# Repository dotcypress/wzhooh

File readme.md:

# Wzhooh

Slot Car Lap Timer

## Resources

- [Web dashboard](https://wzhooh.vercel.app)
- [Schematics](pcb/fab/wzhooh.pdf)
- [Gerber files](pcb/fab/Wzhooh_rev_0x01.zip)
- [BOM](pcb/fab/wzhooh-bom.csv)
- [Interactive BOM](https://htmlpreview.github.io/?https://github.com/dotcypress/wzhooh/blob/main/pcb/fab/ibom.html)

## Installation

1. Download latest firmware build from [Releases page](https://github.com/dotcypress/wzhooh/releases)
2. Hold the BOOTSEL button while connecting your board to the computer
3. Copy firmware file downloaded earlier to the RPi-RP2 disk
4. Enjoy

## Building firmware

1. Install rustup by following the instructions at https://rustup.rs
2. Install Cortex-M0, M0+, and M1 (ARMv6-M architecture) target: `rustup target add thumbv6m-none-eabi`
3. Install LLVM tools: `rustup component add llvm-tools-preview`
4. Install cargo-binutils: `cargo install cargo-binutils` (Note: on some Linux distros (e.g. Ubuntu) you may need to install the packages build-essential, gcc-arm-none-eabi, libssl-dev and pkg-config prior to installing cargo-binutils)
5. Install elf2uf2: `cargo install elf2uf2-rs`
6. Clone this repo: `git clone git@github.com:dotcypress/wzhooh.git && cd wzhooh`
7. Hold the BOOTSEL button while connecting your board to the computer
8. Flash microcontroller: `cargo run --release`

## License

Licensed under either of

- Apache License, Version 2.0 ([LICENSE-APACHE](LICENSE-APACHE) or
  http://www.apache.org/licenses/LICENSE-2.0)
- MIT license ([LICENSE-MIT](LICENSE-MIT) or http://opensource.org/licenses/MIT)

at your option.

### Contribution

Unless you explicitly state otherwise, any contribution intentionally submitted
for inclusion in the work by you, as defined in the Apache-2.0 license, shall be
dual licensed as above, without any additional terms or conditions.

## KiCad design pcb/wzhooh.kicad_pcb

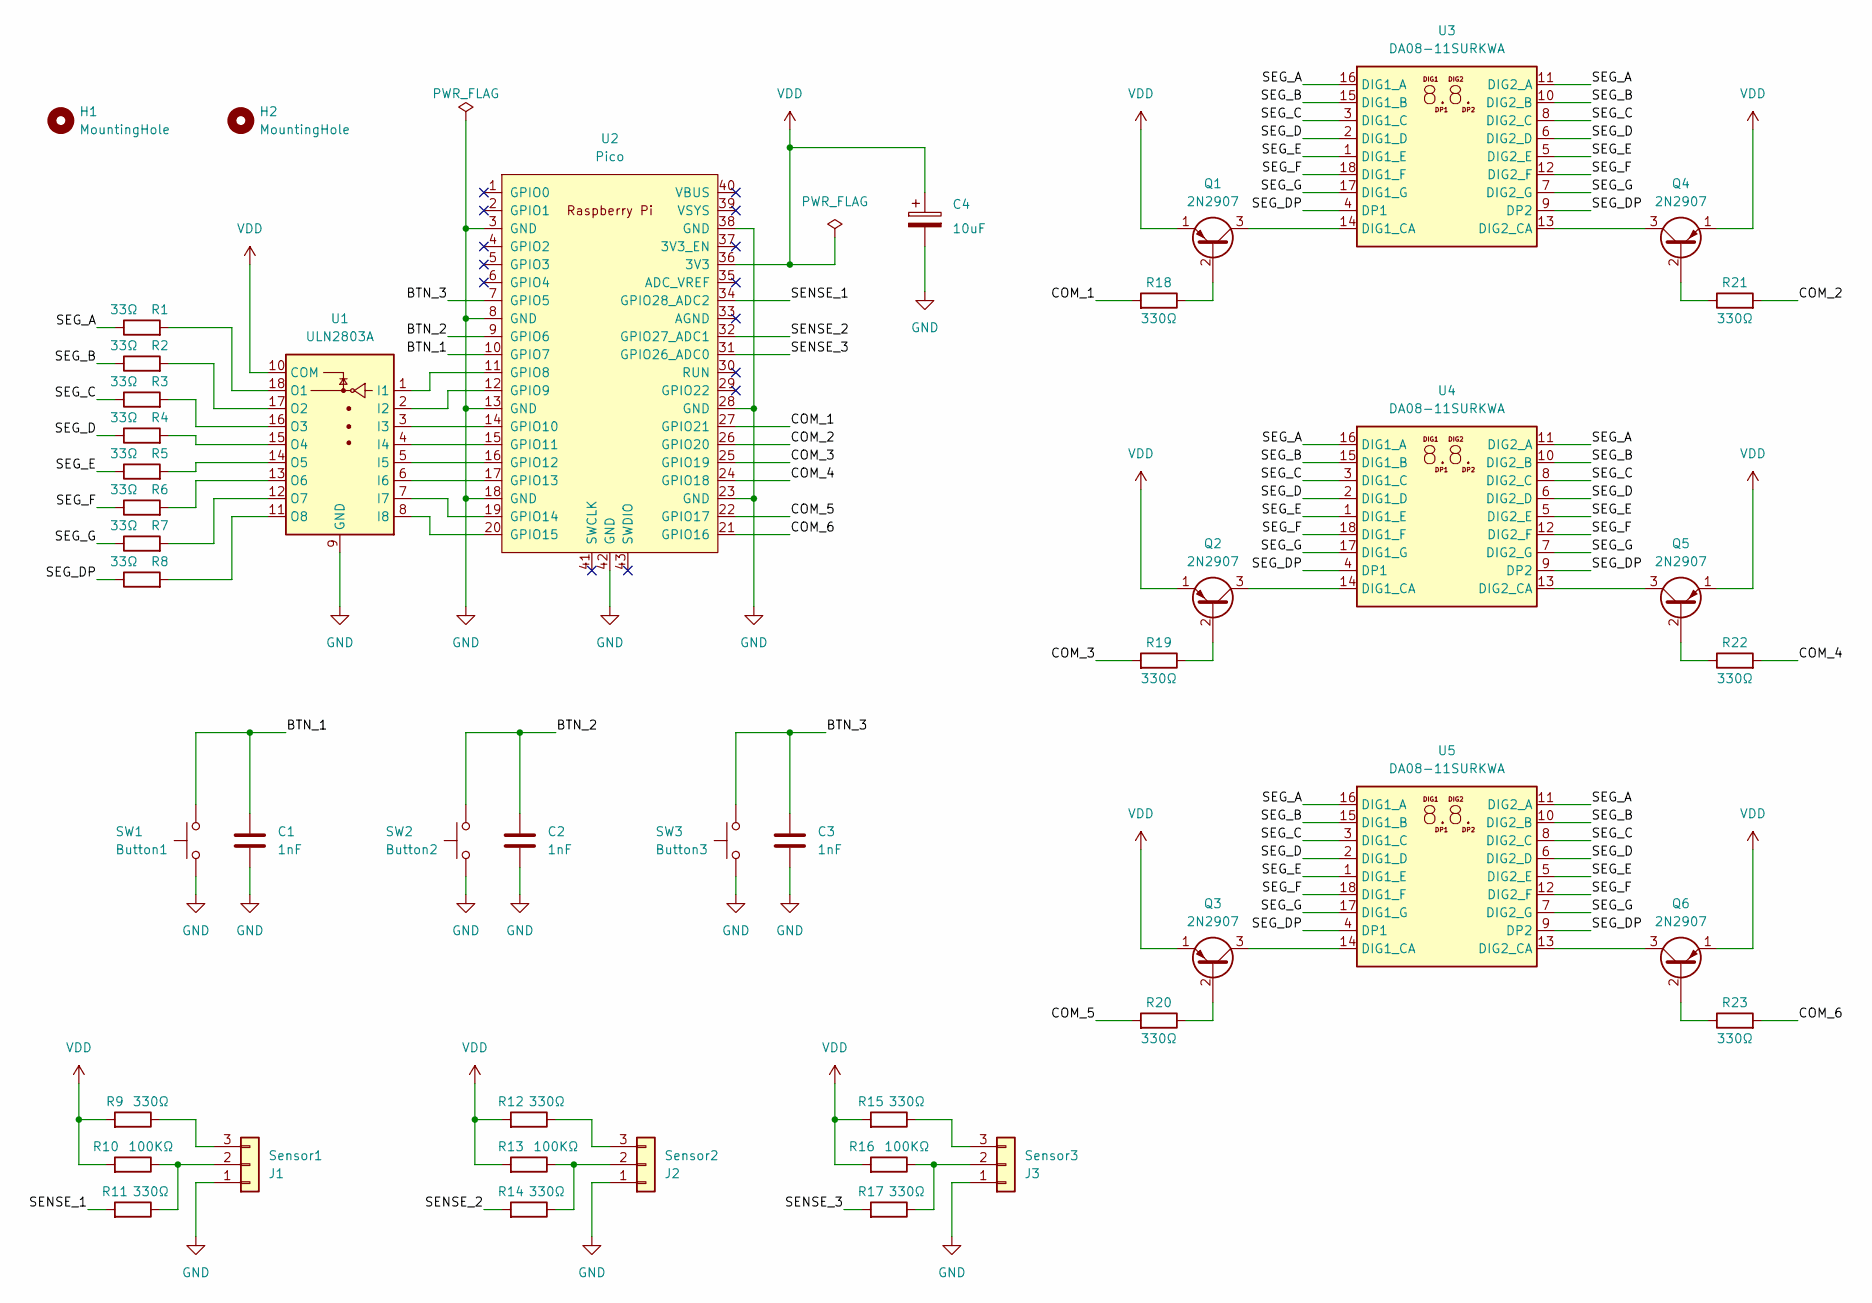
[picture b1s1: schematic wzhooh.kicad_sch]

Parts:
C1, C2, C3: 1nF; C_Disc_D4.7mm_W2.5mm_P5.00mm
C4: 10uF; CP_Radial_D7.5mm_P2.50mm
H1, H2: MountingHole; MountingHole_3.2mm_M3
J1: Sensor1; PinHeader_1x03_P2.54mm_Horizontal
J2: Sensor2; PinHeader_1x03_P2.54mm_Horizontal
J3: Sensor3; PinHeader_1x03_P2.54mm_Horizontal
Q1, Q2, Q3, Q4, Q5: 2N2907; TO-92_Inline
Q6: 2N2907; //www.mouser.com/datasheet/2/849/2n2907a-2577411.pdf
R1, R2, R3, R4, R5, R6, R7, R8: 33Ω; R_Axial_DIN0207_L6.3mm_D2.5mm_P2.54mm_Vertical
R9, R11, R12, R14, R15, R17, R18, R19, R20, R21, R22, R23: 330Ω; R_Axial_DIN0207_L6.3mm_D2.5mm_P2.54mm_Vertical
R10, R13, R16: 100KΩ; R_Axial_DIN0207_L6.3mm_D2.5mm_P2.54mm_Vertical
SW1: Button1; SW_PUSH_6mm_H13mm
SW2: Button2; SW_PUSH_6mm_H13mm
SW3: Button3; SW_PUSH_6mm_H13mm
U1: ULN2803A; DIP-18_W7.62mm
U2: Pico; RPi_Pico_SMD_TH
U3, U4, U5: DA08-11SURKWA; DA08-11

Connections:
/BTN_1: C1.1, SW1.2, U2.10 (GPIO7)
/BTN_2: C2.1, SW2.2, U2.9 (GPIO6)
/BTN_3: C3.1, SW3.2, U2.7 (GPIO5)
/COM_1: R18.2, U2.27 (GPIO21)
/COM_2: R21.2, U2.26 (GPIO20)
/COM_3: R19.2, U2.25 (GPIO19)
/COM_4: R22.2, U2.24 (GPIO18)
/COM_5: R20.2, U2.22 (GPIO17)
/COM_6: R23.2, U2.21 (GPIO16)
/SEG_A: R1.1, U3.11 (DIG2_A), U3.16 (DIG1_A), U4.11 (DIG2_A), U4.16 (DIG1_A), U5.11 (DIG2_A), U5.16 (DIG1_A)
/SEG_B: R2.1, U3.10 (DIG2_B), U3.15 (DIG1_B), U4.10 (DIG2_B), U4.15 (DIG1_B), U5.10 (DIG2_B), U5.15 (DIG1_B)
/SEG_C: R3.1, U3.3 (DIG1_C), U3.8 (DIG2_C), U4.3 (DIG1_C), U4.8 (DIG2_C), U5.3 (DIG1_C), U5.8 (DIG2_C)
/SEG_D: R4.1, U3.2 (DIG1_D), U3.6 (DIG2_D), U4.2 (DIG1_D), U4.6 (DIG2_D), U5.2 (DIG1_D), U5.6 (DIG2_D)
/SEG_DP: R8.1, U3.4 (DP1), U3.9 (DP2), U4.4 (DP1), U4.9 (DP2), U5.4 (DP1), U5.9 (DP2)
/SEG_E: R5.1, U3.1 (DIG1_E), U3.5 (DIG2_E), U4.1 (DIG1_E), U4.5 (DIG2_E), U5.1 (DIG1_E), U5.5 (DIG2_E)
/SEG_F: R6.1, U3.12 (DIG2_F), U3.18 (DIG1_F), U4.12 (DIG2_F), U4.18 (DIG1_F), U5.12 (DIG2_F), U5.18 (DIG1_F)
/SEG_G: R7.1, U3.7 (DIG2_G), U3.17 (DIG1_G), U4.7 (DIG2_G), U4.17 (DIG1_G), U5.7 (DIG2_G), U5.17 (DIG1_G)
/SENSE_1: R11.2, U2.34 (GPIO28_ADC2)
/SENSE_2: R14.2, U2.32 (GPIO27_ADC1)
/SENSE_3: R17.2, U2.31 (GPIO26_ADC0)
GND: C1.2, C2.2, C3.2, C4.2, J1.1, J2.1, J3.1, SW1.1, SW2.1, SW3.1, U1.9 (GND), U2.3 (GND), U2.8 (GND), U2.13 (GND), U2.18 (GND), U2.23 (GND), U2.28 (GND), U2.38 (GND), U2.42 (GND)
unnamed: J1.2, R10.1, R11.1
unnamed: J1.3, R9.1
unnamed: J2.2, R13.1, R14.1
unnamed: J2.3, R12.1
unnamed: J3.2, R16.1, R17.1
unnamed: J3.3, R15.1
unnamed: Q1.2 (B), R18.1
unnamed: Q1.3 (C), U3.14 (DIG1_CA)
unnamed: Q2.2 (B), R19.1
unnamed: Q2.3 (C), U4.14 (DIG1_CA)
unnamed: Q3.2 (B), R20.1
unnamed: Q3.3 (C), U5.14 (DIG1_CA)
unnamed: Q4.2 (B), R21.1
unnamed: Q4.3 (C), U3.13 (DIG2_CA)
unnamed: Q5.2 (B), R22.1
unnamed: Q5.3 (C), U4.13 (DIG2_CA)
unnamed: Q6.2 (B), R23.1
unnamed: Q6.3 (C), U5.13 (DIG2_CA)
unnamed: U1.1 (I1), U2.11 (GPIO8)
unnamed: U1.2 (I2), U2.12 (GPIO9)
unnamed: U1.3 (I3), U2.14 (GPIO10)
unnamed: U1.4 (I4), U2.15 (GPIO11)
unnamed: U1.5 (I5), U2.16 (GPIO12)
unnamed: U1.6 (I6), U2.17 (GPIO13)
unnamed: U1.7 (I7), U2.19 (GPIO14)
unnamed: U1.8 (I8), U2.20 (GPIO15)
unnamed: R1.2, U1.18 (O1)
unnamed: R2.2, U1.17 (O2)
unnamed: R3.2, U1.16 (O3)
unnamed: R4.2, U1.15 (O4)
unnamed: R5.2, U1.14 (O5)
unnamed: R6.2, U1.13 (O6)
unnamed: R7.2, U1.12 (O7)
unnamed: R8.2, U1.11 (O8)
VDD: C4.1, Q1.1 (E), Q2.1 (E), Q3.1 (E), Q4.1 (E), Q5.1 (E), Q6.1 (E), R9.2, R10.2, R12.2, R13.2, R15.2, R16.2, U1.10 (COM), U2.36 (3V3)

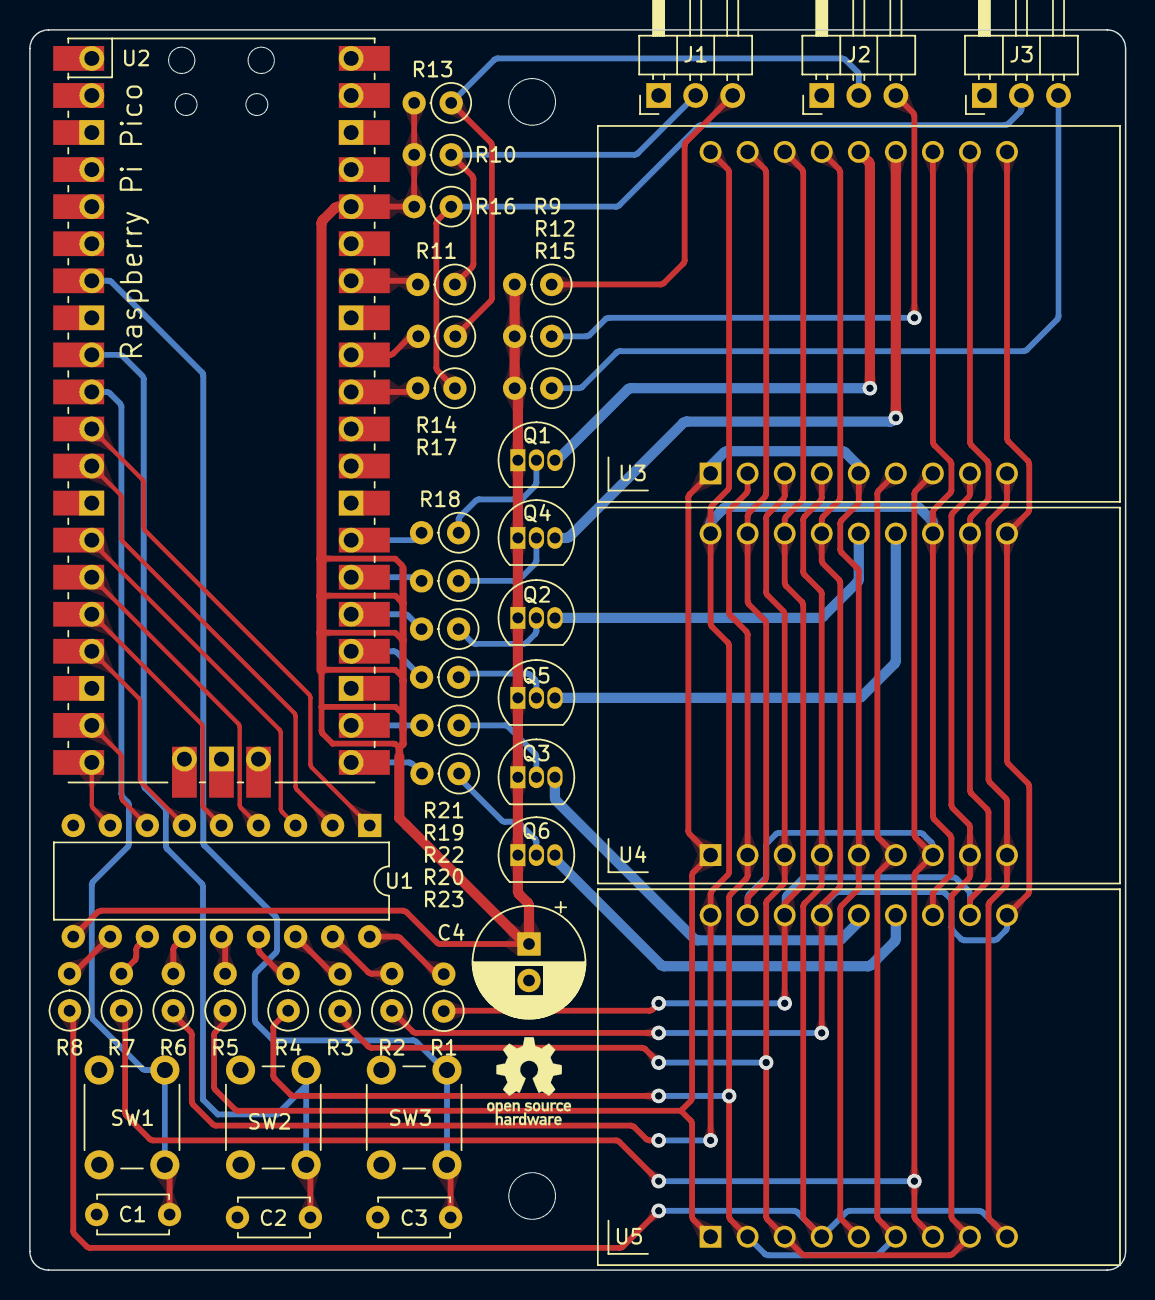
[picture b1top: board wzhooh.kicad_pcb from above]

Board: 2 copper layers, 75.1 x 85.0 mm, 46 parts (0 on the bottom side), 56 nets.

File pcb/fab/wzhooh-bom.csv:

Id,Designator,Footprint,Quantity,Designation,Supplier and ref,,
1,"R11,R22,R20,R21,R14,R12,R9,R17,R19,R18,R23,R15",R_Axial_DIN0207_L6.3mm_D2.5mm_P2.54mm_Vertical,12,330Ω,https://m-teh.com.ua/ru/rezistor-330r-0.25w-cfr-5,,
2,"R4,R6,R8,R7,R5,R3,R2,R1",R_Axial_DIN0207_L6.3mm_D2.5mm_P2.54mm_Vertical,8,33Ω,https://m-teh.com.ua/ru/rezistor-33r-0.25w-cfr-5/,,
6,"C3,C1,C2",C_Disc_D4.7mm_W2.5mm_P5.00mm,3,1nF,https://m-teh.com.ua/ru/kondensator-mcc-0.1uf-50v-x7r-10/,,
7,C4,CP_Radial_D7.5mm_P2.50mm,1,4.7uF,https://m-teh.com.ua/ru/kondensator-ze-330uf-10v-69-[polimerniy]/,,
8,"J1,J2,J3",PinHeader_1x03_P2.54mm_Horizontal,3,Sensors,https://m-teh.com.ua/ru/pls1x40-zl201-40g/,,
9,"U4,U5,U3",DA08-11,3,DA08-11SURKWA,https://m-teh.com.ua/ru/indikator-2-rozryadi-0.8chervoniy-an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,,
10,"R10,R16,R13",R_Axial_DIN0207_L6.3mm_D2.5mm_P2.54mm_Vertical,3,100KΩ,https://m-teh.com.ua/ru/rezistor-100k-0.25w-cfr-5,,
11,"Q3,Q1,Q2,Q4,Q6,Q5",TO-92_Inline,6,2N2907,https://m-teh.com.ua/ru/tranzistor-2n2907/,,
12,U2,RPi_Pico_SMD_TH,1,Pico,https://arduino.ua/prod4358-raspberry-pi-pico,,
13,"SW1,SW2,SW3",SW_PUSH_6mm_H13mm,3,Buttons,https://m-teh.com.ua/ru/knopka-taktova-tact-6x6-7.5,,
16,U1,DIP-18_W7.62mm,1,ULN2803A,https://m-teh.com.ua/ru/sborka-tranzystorov-uln2803apg,,

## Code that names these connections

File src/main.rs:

#![no_std]
#![no_main]

extern crate panic_probe;
extern crate rp2040_hal as hal;
extern crate rtic;

use defmt_rtt as _;

mod counter;
mod display;
mod io;
mod telemetry;

use cortex_m::singleton;
use counter::*;
use display::*;
use embedded_hal::digital::v2::OutputPin;
use hal::gpio::*;
use hal::pac;
use hal::pwm;
use hal::timer::{monotonic::Monotonic, *};
use hal::usb::UsbBus;
use io::*;
use telemetry::*;
use usb_device::class_prelude::*;
use usb_device::prelude::*;
use usbd_webusb::{url_scheme, WebUsb};

pub const XTAL_FREQ_HZ: u32 = 12_000_000_u32;

#[link_section = ".boot2"]
#[no_mangle]
#[used]
pub static BOOT2: [u8; 256] = rp2040_boot2::BOOT_LOADER_GENERIC_03H;

#[rtic::app(device = pac, peripherals = true, dispatchers = [SW0_IRQ, SW1_IRQ])]
mod app {
    use super::*;

    #[monotonic(binds = TIMER_IRQ_0, default = true)]
    type Oracle = Monotonic<Alarm0>;

    #[local]
    struct Local {
        buttons: Buttons,
        sensors: Sensors,
        ui_timer: pwm::Slice<pwm::Pwm0, pwm::FreeRunning>,
        usb_dev: UsbDevice<'static, hal::usb::UsbBus>,
        wusb: WebUsb<hal::usb::UsbBus>,
    }

    #[shared]
    struct Shared {
        display: Display,
        counter: LapCounter,
        telemetry: RaceTelemetryClass<'static, hal::usb::UsbBus>,
    }

    #[init]
    fn init(ctx: init::Context) -> (Shared, Local, init::Monotonics) {
        let mut resets = ctx.device.RESETS;
        let mut watchdog = hal::Watchdog::new(ctx.device.WATCHDOG);
        let clocks = hal::clocks::init_clocks_and_plls(
            XTAL_FREQ_HZ,
            ctx.device.XOSC,
            ctx.device.CLOCKS,
            ctx.device.PLL_SYS,
            ctx.device.PLL_USB,
            &mut resets,
            &mut watchdog,
        )
        .ok()
        .expect("Clocks init failed");

        let sio = hal::Sio::new(ctx.device.SIO);
        let pins = Pins::new(
            ctx.device.IO_BANK0,
            ctx.device.PADS_BANK0,
            sio.gpio_bank0,
            &mut resets,
        );

        let counter = LapCounter::default();

        let sensors = Sensors::new([
            pins.gpio28.into_floating_input().into_dyn_pin(),
            pins.gpio27.into_floating_input().into_dyn_pin(),
            pins.gpio26.into_floating_input().into_dyn_pin(),
        ]);

        let buttons = Buttons::new([
            pins.gpio7.into_pull_up_input().into_dyn_pin(),
            pins.gpio6.into_pull_up_input().into_dyn_pin(),
            pins.gpio5.into_pull_up_input().into_dyn_pin(),
        ]);

        let display = Display::new(
            [
                pins.gpio20.into_push_pull_output().into_dyn_pin(),
                pins.gpio21.into_push_pull_output().into_dyn_pin(),
                pins.gpio18.into_push_pull_output().into_dyn_pin(),
                pins.gpio19.into_push_pull_output().into_dyn_pin(),
                pins.gpio16.into_push_pull_output().into_dyn_pin(),
                pins.gpio17.into_push_pull_output().into_dyn_pin(),
            ],
            [
                pins.gpio8.into_push_pull_output().into_dyn_pin(),
                pins.gpio9.into_push_pull_output().into_dyn_pin(),
                pins.gpio10.into_push_pull_output().into_dyn_pin(),
                pins.gpio11.into_push_pull_output().into_dyn_pin(),
                pins.gpio12.into_push_pull_output().into_dyn_pin(),
                pins.gpio13.into_push_pull_output().into_dyn_pin(),
                pins.gpio14.into_push_pull_output().into_dyn_pin(),
                pins.gpio15.into_push_pull_output().into_dyn_pin(),
            ],
        );

        let pwm_slices = hal::pwm::Slices::new(ctx.device.PWM, &mut resets);
        let mut ui_timer = pwm_slices.pwm0;
        ui_timer.enable_interrupt();
        ui_timer.enable();

        let mut timer = hal::Timer::new(ctx.device.TIMER, &mut resets, &clocks);
        let alarm = timer.alarm_0().expect("Alarm0 init failed");
        let mono = Monotonic::new(timer, alarm);

        let usb_regs = ctx.device.USBCTRL_REGS;
        let usb_dpram = ctx.device.USBCTRL_DPRAM;
        let usb_bus = UsbBus::new(usb_regs, usb_dpram, clocks.usb_clock, true, &mut resets);
        let usb_bus: &'static UsbBusAllocator<UsbBus> =
            singleton!(: UsbBusAllocator<UsbBus> = UsbBusAllocator::new(usb_bus))
                .expect("USB init failed");

        let wusb = WebUsb::new(usb_bus, url_scheme::HTTPS, "wzhooh.vercel.app");
        let telemetry = RaceTelemetryClass::new(usb_bus);

        let usb_dev = UsbDeviceBuilder::new(usb_bus, UsbVidPid(0x1209, 0xb421))
            .manufacturer("vitaly.codes")
            .product("Wzhooh")
            .serial_number("_wzhooh_")
            .build();

        unsafe {
            pac::NVIC::unmask(pac::Interrupt::IO_IRQ_BANK0);
            pac::NVIC::unmask(pac::Interrupt::USBCTRL_IRQ);
        };

        (
            Shared {
                counter,
                display,
                telemetry,
            },
            Local {
                buttons,
                sensors,
                wusb,
                ui_timer,
                usb_dev,
            },
            init::Monotonics(mono),
        )
    }

    #[task(binds = IO_IRQ_BANK0, priority = 3, local = [buttons, sensors])]
    fn io_irq(ctx: io_irq::Context) {
        let now = monotonics::now();
        for track in 0..TRACKS {
            if ctx.local.sensors.is_car_detected(track) {
                io_event::spawn(IoEvent::CarDetected(track, now)).ok();
            }
        }
        for button in [Button::A, Button::B, Button::C] {
            if ctx.local.buttons.is_pressed(button) {
                io_event::spawn(IoEvent::ButtonPressed(button)).ok();
            }
        }
    }

    #[task(binds = USBCTRL_IRQ, priority = 2, local = [wusb, usb_dev], shared = [telemetry])]
    fn usb_irq(ctx: usb_irq::Context) {
        let mut telemetry = ctx.shared.telemetry;
        telemetry.lock(|telemetry| {
            if ctx.local.usb_dev.poll(&mut [ctx.local.wusb, telemetry]) {
                telemetry.send_report();
            }
            telemetry.app_req().map(app_req::spawn);
        });
    }

    #[task(binds = PWM_IRQ_WRAP, local = [ui_timer], shared = [display])]
    fn update_ui(mut ctx: update_ui::Context) {
        ctx.shared.display.lock(|display| display.animate());
        ctx.local.ui_timer.clear_interrupt();
    }

    #[task(capacity = 8, shared = [counter, display, telemetry])]
    fn app_req(ctx: app_req::Context, req: AppRequest) {
        let app_req::SharedResources {
            mut counter,
            mut display,
            mut telemetry,
        } = ctx.shared;

        match req {
            AppRequest::ResetCounter => {
                counter.lock(|counter| counter.reset());
                display.lock(|display| display.reset());
                telemetry.lock(|telemetry| telemetry.send_reset());
            }
            AppRequest::SendCounterState => {
                telemetry.lock(|telemetry| telemetry.send_reset());
                for track in 0..TRACKS {
                    if let Some(stats) = counter.lock(|counter| counter.stats(track)) {
                        telemetry.lock(|telemetry| telemetry.push_track_stats(stats))
                    }
                }
            }
        }
    }

    #[task(capacity = 16, shared = [counter, display, telemetry])]
    fn io_event(ctx: io_event::Context, ev: IoEvent) {
        let io_event::SharedResources {
            mut counter,
            mut display,
            mut telemetry,
        } = ctx.shared;

        match ev {
            IoEvent::CarDetected(track, ts) => {
                if let Some(stats) = counter.lock(|counter| counter.record_lap(track, ts)) {
                    display.lock(|display| display.set_track_laps(track, stats.laps()));
                    telemetry.lock(|telemetry| telemetry.push_track_stats(stats));
                }
            }
            IoEvent::ButtonPressed(_) => {
                app_req::spawn(AppRequest::ResetCounter).ok();
            }
        }
    }
}

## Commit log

2023-08-30 rename project
2023-09-02 pcb rev:0x01
2023-09-06 add BOM
2023-09-07 impl display
2023-09-07 update CI script
2023-09-07 remove flip-link
2023-09-09 rev: 0x01
2023-09-09 update pcb image
2023-09-09 firmware version 0.0.1
2023-09-09 update ibom
2023-09-11 update rp-hal version
2023-09-24 serial shell
2023-09-24 ci test
2023-09-24 web dashboard
2023-09-24 web serial support
2023-09-24 0.0.2
2023-09-24 counter debouncer
2023-09-24 0.0.3
2023-09-24 add service worker
2023-09-25 add web serial polyfil
2023-09-25 remove web serial polyfil
2023-11-18 switch to WebUSB
2023-11-18 fix counter reset bug
2023-11-18 0.1.0
2023-11-18 restore state on page refresh
2023-11-18 0.1.1
2023-11-18 clippy
2023-11-19 cleanup
2023-11-19 update pid/vid
2023-11-19 0.1.2
2023-11-22 fix counter precision
